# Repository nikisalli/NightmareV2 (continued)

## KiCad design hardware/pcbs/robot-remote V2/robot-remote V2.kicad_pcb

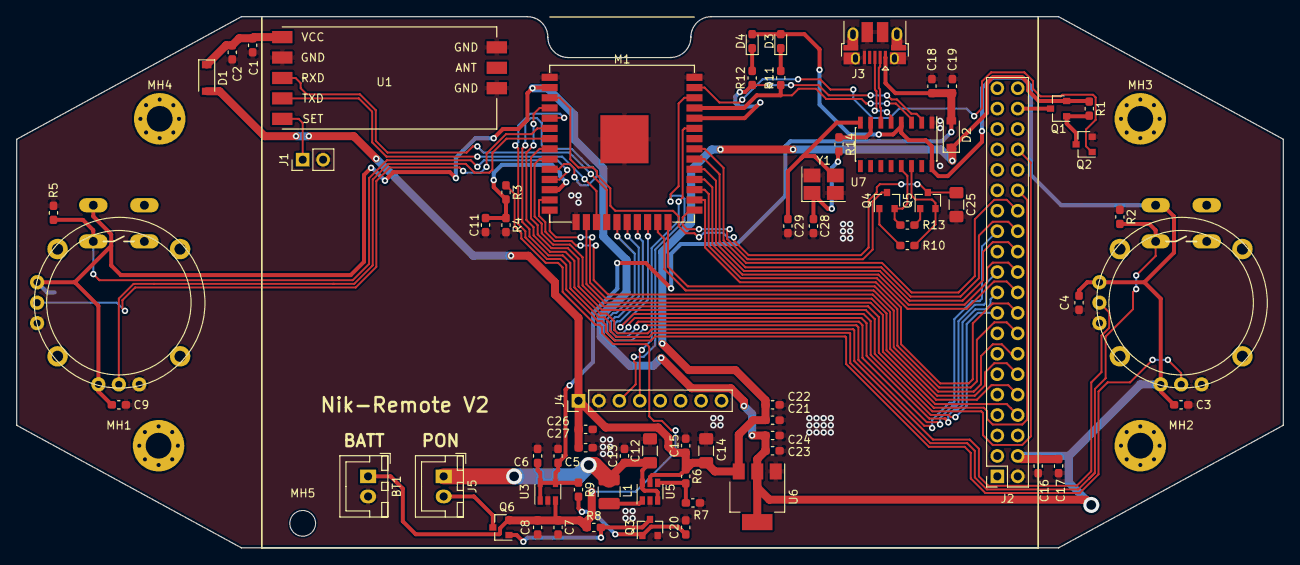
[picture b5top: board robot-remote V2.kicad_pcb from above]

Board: 2 copper layers, 157.5 x 66.0 mm, 74 parts (1 on the bottom side), 59 nets.

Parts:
BT1: Battery; JST_XH_B02B-XH-A_1x02_P2.50mm_Vertical
C1, C3, C5, C8, C9, C11, C16, C18, C20, C21, C23, C26: 1u; C_0603_1608Metric_Pad1.05x0.95mm_HandSolder
C2, C4, C6, C7, C10, C13, C15, C17, C19, C22, C24, C27: 100n; C_0603_1608Metric_Pad1.05x0.95mm_HandSolder
C12, C14, C25: 10u; C_1206_3216Metric_Pad1.42x1.75mm_HandSolder
C28, C29: 22p; C_0603_1608Metric_Pad1.05x0.95mm_HandSolder
D1, D2: 1N5819; D_SOD-123
D3, D4: LED; LED_0603_1608Metric_Pad1.05x0.95mm_HandSolder
J1: Conn_01x02_Male; PinHeader_1x02_P2.54mm_Vertical
J2: Conn_02x20_Odd_Even; PinSocket_2x20_P2.54mm_Vertical
J3: USB_B_Micro; USB_Micro-B_Amphenol_10103594-0001LF_Horizontal
J4: Conn_01x08_Male; PinHeader_1x08_P2.54mm_Vertical
J5: Conn_02x01; JST_XH_B02B-XH-A_1x02_P2.50mm_Vertical
L1: INDUCTOR; L_1210_3225Metric_Pad1.42x2.65mm_HandSolder
M1: ESP-32S
MH1, MH2, MH3, MH4: MountingHole; MountingHole_3.2mm_M3_Pad_Via
MH5: MountingHole; MountingHole_3.2mm_M3_ISO14580
Q1, Q6: Q_PMOS_GSD; SOT-23
Q2, Q3: 2N7002; SOT-23
Q4, Q5: S8050; SOT-23
R1, R4, R9, R11, R12: 1k; R_0603_1608Metric_Pad1.05x0.95mm_HandSolder
R2, R3, R5, R8: 10k; R_0603_1608Metric_Pad1.05x0.95mm_HandSolder
R6, R7: R; R_0603_1608Metric_Pad1.05x0.95mm_HandSolder
R10, R13: 12k; R_0603_1608Metric_Pad1.05x0.95mm_HandSolder
R14: 220R; R_0603_1608Metric_Pad1.05x0.95mm_HandSolder
U1: HC-12
U2, U4: JOYSTICKPTH; JOYSTICK
U3: MCP73811T; SOT-23-5
U5: MCP1640BCH; SOT-23-6
U6: AMS1117-3.3; SOT-223-3_TabPin2
U7: CH340G; SOIC-16_3.9x9.9mm_P1.27mm
Y1: 12Mhz; Crystal_SMD_SeikoEpson_TSX3225-4Pin_3.2x2.5mm_HandSoldering

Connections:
+3V3: C3.1, C4.1, C9.1, C10.1, C16.1, C17.1, C23.1, C24.1, D3.2, D4.2, J2.4, M1.2, U2.B1A, U2.H1, U2.V1, U4.B1A, U4.H1, U4.V1, U6.2, U7.4, U7.16
+5V: C14.1, C15.1, C21.1, C22.1, C26.1, C27.1, D1.2, D2.1, J4.1, Q1.2, R1.1, R6.1, U5.5, U6.3
BAT_ADC: C11.1, M1.12, R3.2, R4.1
BST_EN: Q3.3, Q6.1, R8.2
EN: C25.1, M1.3, Q5.3
FDO: J2.25, M1.19
F_CLK: J2.17, M1.22
F_CS: J2.19, M1.21
F_DIN: J2.21, M1.20
GND: BT1.2, C1.2, C2.2, C3.2, C4.2, C5.2, C6.2, C7.2, C8.2, C9.2, C10.2, C11.2, C12.2, C13.2, C14.2, C15.2, C16.2, C17.2, C18.2, C19.2, C20.2, C21.2, C22.2, C23.2, C24.2, C25.2, C26.2, C27.2, C28.2, C29.2, J1.2, J2.2, J3.5, J3.6, J4.2, M1.1, M1.15, M1.38, Q2.2, Q3.2, R2.1, R4.2, R5.1, R7.2, U1.2, U1.6, U1.8, U2.H3, U2.V3, U3.2, U4.H3, U4.V3, U5.2, U6.1, U7.1, Y1.2, Y1.4
IO0: M1.25, Q4.3
J_H1: M1.5, U2.H2
J_H2: M1.7, U4.H2
J_SW1: M1.10, R2.2, U2.B2A
J_SW2: M1.11, R5.2, U4.B2A
J_V1: M1.4, U2.V2
J_V2: M1.6, U4.V2
unnamed: C1.1, C2.1, D1.1, U1.1
unnamed: C12.1, C13.1, J5.1, L1.1, U5.3, U5.6
unnamed: C20.1, Q3.1, R9.2
unnamed: C28.1, R14.2, Y1.1
unnamed: C29.1, U7.8, Y1.3
unnamed: D3.1, R11.2
unnamed: D4.1, R12.2
unnamed: J1.1, U1.5
unnamed: J3.2, U7.6
unnamed: J3.3, U7.5
unnamed: J5.2, Q6.3
unnamed: L1.2, U5.1
unnamed: Q1.1, Q2.3, R1.2
unnamed: Q4.1, R10.1
unnamed: Q4.2, R13.2, U7.13
unnamed: Q5.1, R13.1
unnamed: Q5.2, R10.2, U7.14
unnamed: R6.2, R7.1, U5.4
unnamed: R14.1, U7.7
SCL: J4.3, M1.36
SDA: J4.4, M1.33
S_RX: M1.17, U1.4
S_TX: M1.18, U1.3
T_BL: M1.37, Q2.1
T_CS: J2.30, M1.9
T_D8: J2.14, M1.23
T_D9: J2.16, M1.24
T_D10: J2.18, M1.26
T_D11: J2.20, M1.27
T_D12: J2.22, M1.28
T_D13: J2.24, M1.29
T_D14: J2.26, M1.30
T_D15: J2.28, M1.31
T_LED: J2.38, Q1.3
T_RD: J2.12, M1.13
T_RS: J2.8, M1.16
T_RST: J2.34, M1.8
T_WR: J2.10, M1.14
USB_RX: M1.35, R11.1, U7.3
USB_TX: M1.34, R12.1, U7.2
VBUS: BT1.1, C7.1, C8.1, Q6.2, R3.1, R8.1, U3.3
VDD: C5.1, C6.1, C18.1, C19.1, D2.2, J3.1, R9.1, U3.1, U3.4, U3.5

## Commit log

2019-07-21 added forward kinematics
2019-07-22 added simulators for legs etc.
2019-07-22 added many hardware files
2019-09-15 added gitignore
2019-09-15 just a test
2019-09-19 added Nik remote app
2019-09-19 removed one useless commented piece of code
2019-09-23 added bew
2019-09-23 Revert "added bew"
    This reverts commit 4cd9bb830ea2021bc2d5ab4e9bfde4d9b52f6f8b.
2019-09-23 Revert "Revert "added bew""
    This reverts commit eaa0afc83e306b20398fbf5df645c42d72c83231.
2019-09-23 added bew simulator
2019-09-25 added new fast walking gait
2019-09-26 speeded up 4x4 gait
2019-09-27 added gait selector in nik remote app
2019-09-27 minor fix on speed limit bug
2019-10-16 android studio changes
2019-10-16 added leg controller
2019-10-25 changed constructors
2019-10-25 changed defines with constant variables
2019-10-25 stupido nik
2019-10-26 cleaned up the step method
2019-10-26 redecleared Dlegs global to avoid redeclaration in servos.cpp
2019-10-26 class Octapod is now a singleton
2019-10-26 changed web updater task priority
2019-10-27 removed some magic numbers and added utility functions for servo management
2019-11-01 hc12 is not a class anymore
2019-11-01 Nightmare has benn promoted to namespace
2019-11-06 added leg simulator
2019-11-22 fixed borders on pcb not being closed
2019-11-27 changed kicad version
2019-11-27 renamed code directory and added lattepanda boot control logic (Tested on hw)
2019-11-28 removed all OTA updater related things
2019-11-28 removed ota related defines
2019-11-28 nothing
2019-11-28 aligned one comment
2019-11-29 added ros workspace
2019-11-29 realized it was a bad idea
2019-11-29 initial ros package commit
2019-11-29 added roscpp and std_msgs deps
2019-11-29 added listener initial code
2019-11-30 made first working parameter talker and listener
2019-11-30 changed panda packet header
2019-11-30 added current measure
2019-11-30 solved python warnings and made faster ros node
2019-11-30 added example onboard imu code
2019-12-06 added covariance matrices to pose estimation kalman filter
2019-12-07 added primary nightmare imu code
2019-12-08 added body roll pitch and yaw topic
2019-12-08 removed old debugging code
2019-12-16 added urdf (3d model for ros)
2019-12-19 added joint position control and joint data stream
2019-12-24 fixed urdf and added pin names to pcb
2019-12-24 servowrite and bodytoservos aren't bool anymore
2019-12-24 fixed some comments in define.h
2019-12-25 added some comments to python file
2019-12-25 solved critical bug that completely broke robot kinematics
2019-12-25 fixed bug that limited refresh rate to 2fps
2019-12-25 solved bug that sends wrong angles to panda
2019-12-25 final bug fix, now everything seems to work fine
2019-12-26 fixed 3d model center position
2019-12-28 added camera link to the body
2020-01-04 added servo init sequence (BROKEN NEEDS BUGFIX)
2020-01-06 (STILL BROKEN AND NEEDS BUGFIX)
2020-02-06 fixed forward kinematics
2020-02-18 added new python nightcontrol app
2020-02-18 fixed mispelled topic name
2020-02-19 added gauge but cannot get it to work on opengl3
2020-03-03 fixed GL rendering bug and gui alignment
2020-03-23 added 3d models and pcbs
2020-03-26 added niktab joystick firmware
2020-04-08 fixed some graphics
